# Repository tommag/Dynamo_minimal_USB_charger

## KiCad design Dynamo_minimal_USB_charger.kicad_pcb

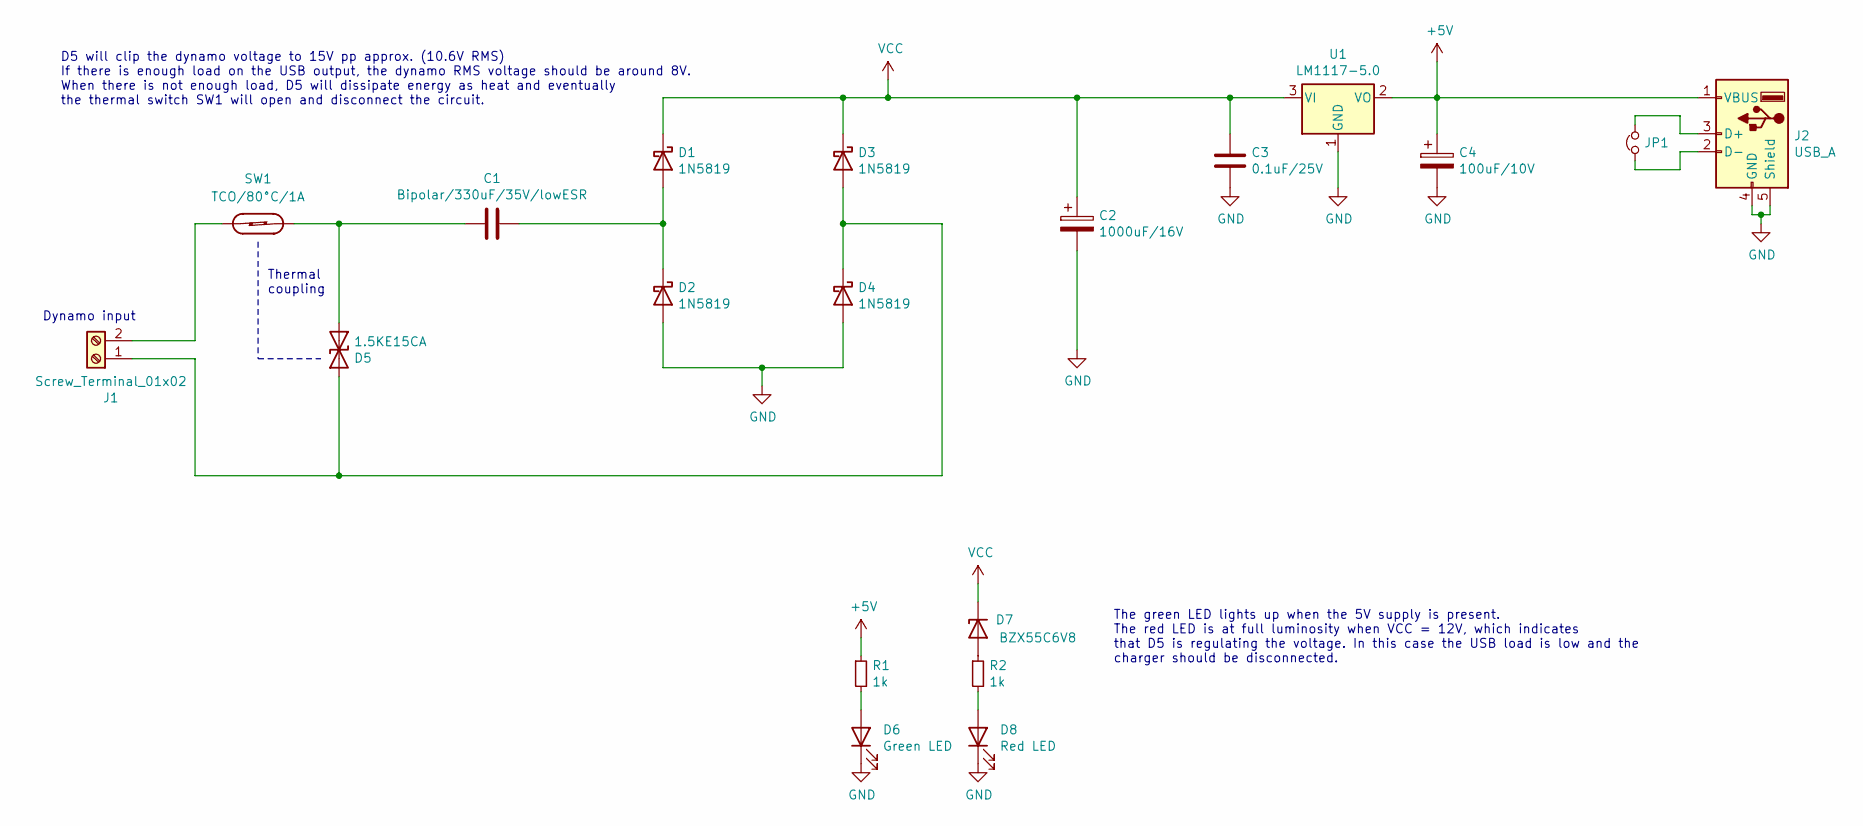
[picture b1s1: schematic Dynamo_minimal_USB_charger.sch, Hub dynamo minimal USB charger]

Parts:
C1: Bipolar/330uF/35V/lowESR; C_Radial_D12.5mm_H20.0mm_P5.00mm
C2: 1000uF/16V; CP_Radial_D12.5mm_P5.00mm
C3: 0.1uF/25V; C_Disc_D4.3mm_W1.9mm_P5.00mm
C4: 100uF/10V; CP_Radial_D4.0mm_P2.00mm
D1, D2, D3, D4: 1N5819; D_DO-41_SOD81_P7.62mm_Horizontal
D5: 1.5KE15CA; D_DO-201AE_P12.70mm_Horizontal
D6: Green LED; LED_D3.0mm_Horizontal_O1.27mm_Z2.0mm
D7: BZX55C6V8; D_DO-35_SOD27_P7.62mm_Horizontal
D8: Red LED; LED_D3.0mm_Horizontal_O1.27mm_Z2.0mm
J1: Screw_Terminal_01x02; TerminalBlock_Phoenix_MKDS-1,5-2_1x02_P5.00mm_Horizontal
J2: USB_A; USB_A_Molex_67643_Horizontal
JP1: Jumper_NC_Small; SolderJumper-2_P1.3mm_Bridged_RoundedPad1.0x1.5mm
R1, R2: 1k; R_Axial_DIN0207_L6.3mm_D2.5mm_P7.62mm_Horizontal
SW1: TCO/80°C/1A; SolderWire-0.5sqmm_1x02_P4.8mm_D0.9mm_OD2.3mm
U1: LM1117-5.0; TO-252-2

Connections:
+5V: C4.1, J2.1 (VBUS), R1.1, U1.2 (VO)
GND: C2.2, C3.2, C4.2, D2.2 (A), D4.2 (A), D6.1 (K), D8.1 (K), J2.4 (GND), J2.5 (Shield), U1.1 (GND)
unnamed: C1.1, D1.2 (A), D2.1 (K)
unnamed: C1.2, D5.2 (A2), SW1.2
unnamed: D3.2 (A), D4.1 (K), D5.1 (A1), J1.1
unnamed: D6.2 (A), R1.2
unnamed: D7.2 (A), R2.1
unnamed: D8.2 (A), R2.2
unnamed: J1.2, SW1.1
unnamed: J2.2 (D-), JP1.1
unnamed: J2.3 (D+), JP1.2
VCC: C2.1, C3.1, D1.1 (K), D3.1 (K), D7.1 (K), U1.3 (VI)

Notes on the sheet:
Thermal coupling
The green LED lights up when the 5V supply is present. The red LED is at full luminosity when VCC = 12V, which indicates that D5 is regulating the voltage. In this case the USB load is low and the charger should be disconnected.
D5 will clip the dynamo voltage to 15V pp approx. (10.6V RMS) If there is enough load on the USB output, the dynamo RMS voltage should be around 8V. When there is not enough load, D5 will dissipate energy as heat and eventually the thermal switch SW1 will open and disconnect the circuit.
Dynamo input

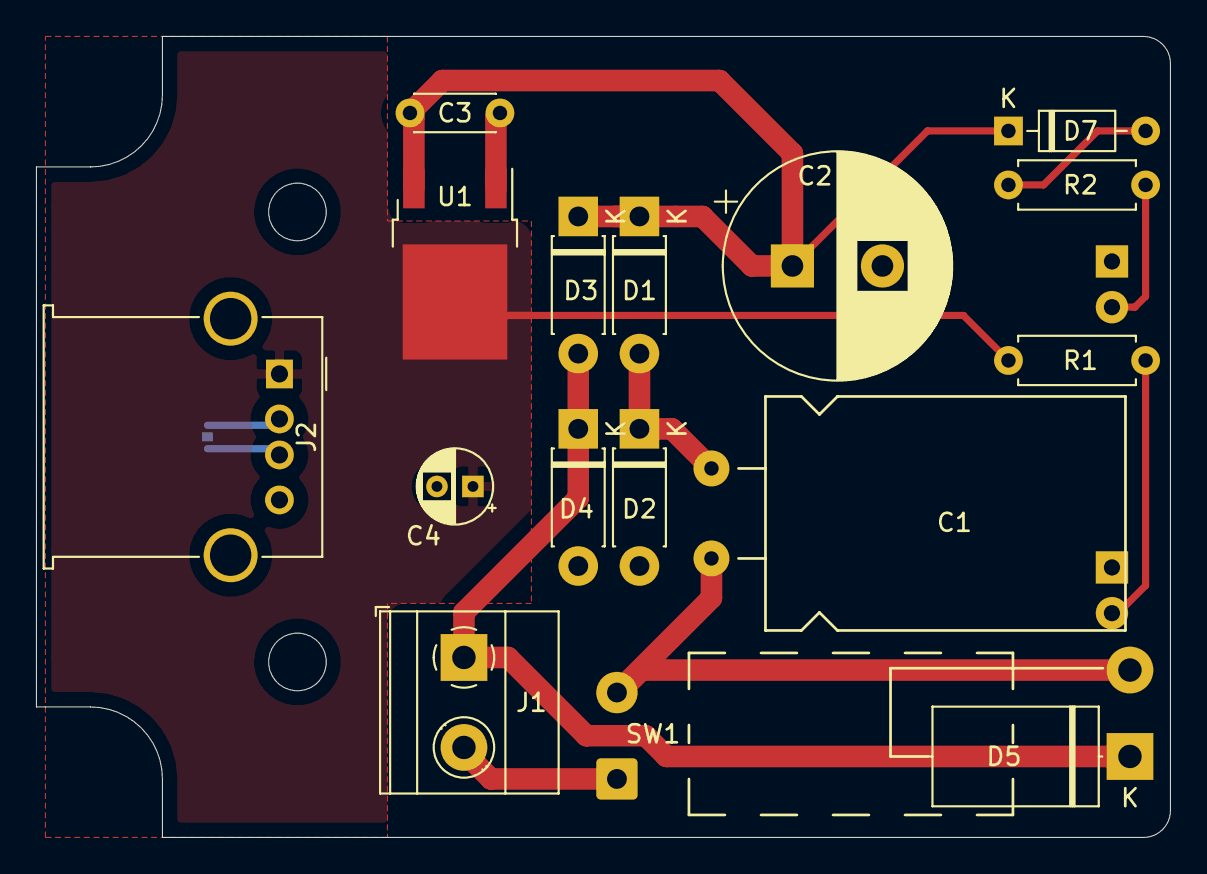
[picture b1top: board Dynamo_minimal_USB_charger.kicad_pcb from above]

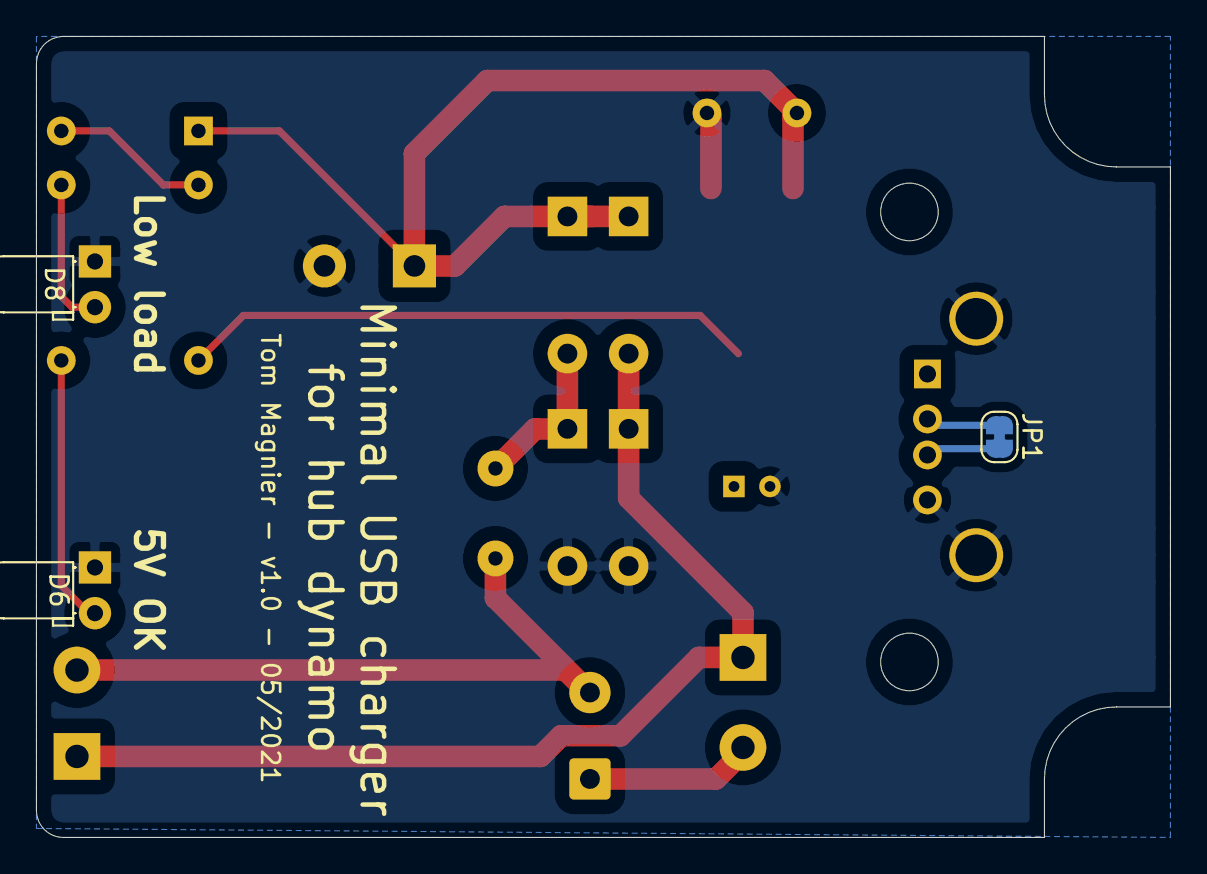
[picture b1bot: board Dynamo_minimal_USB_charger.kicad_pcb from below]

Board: 2 copper layers, 63.0 x 44.5 mm, 19 parts (3 on the bottom side), 12 nets.
